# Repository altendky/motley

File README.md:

# Motley

Motley is a modular embedded-control project for building connected devices
without rebuilding the hardware integration and firmware infrastructure for
every application. The starting platform is ESP32-C6, C++, and Matter over
Thread, with Home Assistant as the initial integration target.

The first application is temperature control and humidity monitoring for an
animal enclosure. The broader goal is a reusable foundation for DIY sensing
and control: combine the boards you need, write application-specific behavior,
and reuse the sensor, output, storage and network integration.

**Early development:** the repository contains a buildable Matter identity
foundation and exploratory KiCad schematics and routed boards. Sensor drivers,
regulation algorithms, output-module firmware and the Matter application
interface are still to be implemented. The boards are designs to develop and
review, not tested products or a manufacturing release.

## Writing applications

The intended programming model keeps application decisions in a portable C++
core. It receives measurements, time and operation results, updates its state,
and describes the work it wants performed. Adapters handle sensors, outputs,
persistent storage and Matter; the same application logic can run in host tests
with controlled inputs.

For the enclosure application, that means concentrating on which sensor controls
which heater, setpoints, control modes, limits and fault responses. New
applications should be able to reuse the surrounding infrastructure rather
than couple their decisions directly to ESP-IDF or Matter APIs. This separation
is the [planned architecture](.rqml/adr/0001-portable-core-and-adapters.md);
an application framework and example application are still future work.

Extensibility includes separate sensor and output boards, addressed expansion,
and Qwiic access to both controller I2C buses. Additional interfaces, displays
and local controls are being considered. The hardware and software are intended
to grow through useful applications rather than require a fixed enclosure or
sensor/output count.

## First application: enclosure thermal control

The initial arrangement puts the controller outside a humid enclosure, with
remote temperature/humidity probes inside. Two independently controlled AC
heater or lamp outputs are planned, with a starting design target of **300 W
of resistive load per output at nominal 120 VAC**.

Planned output modes include slow, zero-cross-aligned whole-cycle switching for
heaters and phase-angle control for lamps. Each output module has its own MCU
for line-synchronous operation, current and voltage observations, and a series
cutoff relay. Temperature regulation will run locally in the device so it can
continue without Home Assistant or network access.

Exact regulation algorithms, sensor assignments, communication-loss policies
and the Matter control/reporting model are being defined. Higher output ratings,
international mains support and inductive loads are separate investigations;
the component ratings do not establish a finished system rating.

## Board designs

There are three KiCad designs. The initial two-output device uses one controller,
two copies of the output board and one sensor board. All currently use four
copper layers with ground/power planes and components on the front side.

| Board | High-level capabilities | Current outline |
| --- | --- | --- |
| [Controller and AC input](hardware/controller/motley-carrier.kicad_pro) | ESP32-C6 with 8 MB flash; Matter/Thread platform; isolated 5 V mains supply; automatic mains/USB logic-power selection; separately switched sensor supply; both I2C buses exposed through Qwiic; output connections and shared line timing | 95 × 80 mm |
| [Single AC output](hardware/controller/motley-ac-output.kicad_pro) | Local STM32 MCU; triac with random-phase isolated drive; series cutoff relay; isolated current/voltage feedback; branch fuse and configurable snubber; programming/recovery access | 90 × 87 mm |
| [Sensor multiplexer](hardware/controller/motley-sensors.kicad_pro) | Eight independently selected I2C branches with JST-SH/Qwiic-compatible connectors; selectable mux address; deployment and Qwiic upstream connections; cut-down layout for fewer ports | L-shaped, 80 × 40 mm overall |

The preferred expansion target is at least sixteen output boards, subject to
bus and power-budget work. Eight mux addresses provide sensor expansion, also
subject to electrical limits. These are design directions, not demonstrated
maximum configurations. Qwiic is a 3.3 V interface here; it is not the mains or
output-actuator power connection.

See the [board images](hardware/controller/generated/board-images/README.md)
for each copper layer, and the [hardware guide](hardware/controller/README.md)
for interfaces, preliminary parts and remaining engineering work.

## First development-build budget

These are **estimated costs in USD using the upper completion allowance, with
batch totals rounded to the nearest $25**, updated 2026-11-15 for the four-layer,
intelligent-output design. They combine actual
JLCPCB Economic fabrication/assembly quotes from that date's Gerbers and BOM/CPL
with estimated remaining hand-fitted parts and enclosure wiring. JLC's quotes
cover the selected available parts; they do not cover a complete device.
The subsequent exact-part revision has a
[new JLC quotation](docs/jlcpcb-quote-2026-11-16-exact-parts.md): $285.26 /
$312.08 / $419.13 for fabrication and partial assembly in the three scenarios.
The complete-controller budget below still uses the November 15 completion
allowances and needs reconciliation against those newer factory selections.

One complete controller means one controller board, one eight-port sensor board
and two output boards. Small-order minimums mean paying for spare boards even
when finishing only one device.

| Completed controllers | Boards assembled: controller / sensor / output | Estimated total batch cost | Per two-output controller |
| --- | --- | ---: | ---: |
| 1, minimum Economic assembly case | 2 / 2 / 2 | $350 | $350 |
| 2 | 2 / 2 / 5 | $450 | $225 |
| 5 | 5 / 5 / 10 | $800 | $160 |

Per-controller figures divide the rounded batch budget by the number finished,
including the cost of paid-for spares.

The allowance includes PCB fabrication and partial factory assembly, parts to
finish the required boards, heatsinks, mains cord/entry, outlets, panel USB and
internal wiring. Remaining parts require hand assembly. It excludes probes and
extensions, enclosure/mounting hardware, tools, shipping, tax and tariffs.
The selected [7Semi SHT45 probes](https://7semi.com/7semi-sht45-digital-humidity-and-temperature-sensor-probe/)
are about $13 each; probe count is independent of the eight available ports.

See the [budget basis](docs/development-build-costs.md) for quantity assumptions,
quoted charges, remaining-parts allowances and uncertainty. Part sourcing and
assembly eligibility can materially change these figures.

## Explore or contribute

- [Open work](https://github.com/altendky/motley/issues): current hardware,
  application and integration decisions.
- [Hardware candidates](docs/hardware-candidates.md) and
  [output-module design](docs/ac-output-module.md): component research and
  architectural context.
- [Development tools](docs/tooling.md), [firmware build](docs/firmware-build.md)
  and [Matter development](docs/matter-development.md): working with the code.
- [Requirements](requirements.rqml) and [architecture decisions](.rqml/adr/):
  agreed obligations, draft proposals and their rationale.

The first useful contributions are likely to be application design, firmware,
hardware review and practical packaging. Requirements distinguish planned
behavior from implementation and verification; build and CAD checks alone do
not establish that the assembled device works.

## Licensing

Original software and general text are licensed under **MIT OR Apache-2.0**.
Original hardware designs, including independently created symbols and
footprints, are licensed under **CERN-OHL-P-2.0**. Upstream-derived reusable
library parts retain their identified licenses and exceptions.

See the [license scope](LICENSE.md), [complete license texts](LICENSES/) and
[third-party notices](THIRD_PARTY_NOTICES.md).

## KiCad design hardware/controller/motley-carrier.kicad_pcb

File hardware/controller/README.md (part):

# Exploratory modular controller

Status: exploratory design, revised 2026-11-16; not a fabrication release.
All three PCB designs now use **four copper layers**, with low-voltage inner
ground and power planes and front-only assembly. Packed outlines are
**95 x 80 mm** for the carrier, **90 x 87 mm** for each output and an
**80 x 40 mm L** for the sensor board. The current
[four-layer review](four-layer-review.md) records the stackup, connected plane
regions, checks and remaining limits. Earlier
[output](output-routing-review.md) and
[carrier/sensor](carrier-sensor-routing-review.md) routing studies retain the
preceding two-layer evidence.
The [AC passive review](ac-passive-review.md) records the subsequent pulse-rated
component selection and LOW/HIGH assembly variants. The
[current JLC quote](../../docs/jlcpcb-quote-2026-11-16-exact-parts.md) includes the new LOW
passives in Economic assembly; physical electrical qualification remains pending.
The [exact purchasing selections](../../docs/hardware-exact-selections.md)
resolve the remaining connector/holder choices and record their mechanical
integration, including a LOW-only limit on the covered snubber caps. GOOSVN
mains terminals and JST PH output-bus headers pass actual Economic factory
assembly matching. Retail OGN holders, Samtec configuration headers and the
retained Omron relay remain hand-fitted in the current stock situation.
The later DNP USB-header/CC extension adds no default purchased components;
the quote retains its earlier input hashes and is not a new copper-revision quote.

The [intelligent-output review](intelligent-output-review.md) records the current
pin, default-state, power and ESD assessments, including the complete fresh
component/pin inventory. It supersedes the earlier direct-GPIO output portions
of the [pin-bias review](pin-bias-review.md). Output boards now have local MCUs,
isolated current/voltage observations and a shared buffered line reference.
Sensor-enable remains GPIO11 with a local 10k pull-down; sensor-bus reset pulls
still need off-domain review. Loaded drive, temperature/leakage, power budgets,
timing and contact-loss transients remain unqualified. Structural checks do not
close draft `MOT-HW-001/002` or qualify hardware defaults.

Native files now have hidden `Requirements` fields and explicit RQML links.
`uv run scripts/hardware_trace.py` checks 20 native source files and all 269
design footprints by hierarchical UUID identity. The fields record electrical
design applicability; MOT-HW-003 file links cover annotation integrity and
whole-file drift, not completion of the draft electrical requirements.
The fresh schematic inventory is 259 components / 737 symbol-pin identities
across the three designs; two output copies give 338 components / 942 pins per
complete unit. The 269 PCB footprints include ten board-only mechanical items.

The [ESD and access review](esd-access-review.md) records the added connector
clamps, per-port 100 ohm series resistors, marked local-GND touch copper and
optional wire-loop/post probe points. Its previous $3.31 protection estimate is
historical; the additional output bus/SYNC/power protection has not been requoted.
Bare access features require no purchased contacts. All fitted sensor components,
including
upstream clamps D60/D61 and the bare touch pad, are on the front. All boards
have top-side touch access, and assembly remains single-sided. System ESD,
clamp coordination, panel CC/shield and touch/clip qualification remain open.

## Scope and requirements boundary

This KiCad study makes the discussed controller, mux, probe and heater choices
concrete for review. The developer selected **three designs and four physical
boards per unit**: one integrated ESP32-C6 controller with AC input and isolated supply, two identical
single-output AC modules, and one mux with sensor connectors.
[ADR-0011](../../.rqml/adr/0011-single-output-modules-and-sensor-core.md)
records the board partition; [ADR-0014](../../.rqml/adr/0014-integrated-controller-and-switched-sensor-supply.md)
records the integrated controller and sensor supply. [Hardware candidates](../../docs/hardware-candidates.md)
records preliminary parts and unresolved engineering questions.

Under `MOT-PROC-001`, this remains a scoped exploratory exception for reviewing
schematics, interfaces, placement and trimming geometry before agreeing maintained
hardware requirements. It does not approve a mains design, implement firmware,
or qualify a PCB. `GOAL-MOT-SENSING` and `MOT-SENS-005` remain draft. Native
traceability tooling implements approved MOT-HW-003, while the electrical
study uses design-input relationships without claiming hardware verification.

The board experiments use four-layer routing and low-voltage ground/power
planes while retaining front-only assembly. The AC passive revision updates the
gate, snubber and voltage/timing detector networks on those routed studies.
Footprint/current/insulation qualification, enclosure
design, manufacturing release, purchasing and energization remain outside this
experiment. Passing structural checks does not establish mains safety or
functioning trimmed sensor boards.

## Open and review

Open any of these KiCad 10 projects in this directory using the
[pinned mise installation](../../docs/tooling.md#kicad); each has its own matching
root schematic, netlist and PCB:

| Project | Quantity per unit | Physical contents | Trial outline |
| --- | ---: | --- | --- |
| [motley-carrier.kicad_pro](motley-carrier.kicad_pro) | 1 | WROOM-N8, panel USB harness interface, automatic power selector, separate controller/sensor regulators, AC input, main fuse, MEAN WELL IRM-05-5, shared isolated line reference and inter-board connections | 95 x 80 mm |
| [motley-ac-output.kicad_pro](motley-ac-output.kicad_pro) | 2 identical copies | One output: STM32C011 and local logic supply/recovery, random-phase optotriac/triac, cutoff relay, isolated voltage/current feedback, branch fuse, configurable snubber, outlet and heatsink reservation; packed routing study | 90 x 87 mm |
| [motley-sensors.kicad_pro](motley-sensors.kicad_pro) | 1 | TCA9548A and support parts, upstream interface, eight QT sensor ports with pull-ups | L-shaped, 80 x 40 mm overall |

The former `motley-controller` monolithic root/project/PCB is replaced by these
three projects. Shared libraries remain in this directory. No board is panelized
with another, and no mechanical mating height or installed orientation is fixed.
The shapes are movable starting geometry, not minimum-size or enclosure claims.

**Stackup:** F.Cu signals/components, In1.Cu low-voltage GND, In2.Cu separate
low-voltage supply regions, B.Cu signals. The carrier additionally has an In2
GND corridor directly beneath its back-side USB pair. Raw actuator 5 V,
selected logic 5 V, controller 3.3 V and switched sensor 3.3 V remain distinct;
planes do not bypass source selection, switches or Qwiic power links. Mains and
PE retain their external-layer conductors, with no mains/PE planes. Antenna
and sensor-cut exclusions cover all four layers. [ADR-0021](../../.rqml/adr/0021-four-layer-ground-and-power-planes.md)
records the nominal 1.6 mm JLC04161H-7628 study construction and its limits.

**Board-size target:** keep each individual board's overall outline width and
height at or below **100 mm**, including the full untrimmed sensor board.
Exactly 100 mm meets the target. If design work suggests either dimension may
need to exceed it, raise the proposed size, reasons and alternatives with the
developer before proceeding with that enlargement. Larger boards can be agreed;
this is a strong target and discussion trigger, not a hard dimensional limit.
The sensor common area's width/depth trade remains flexible within this target.
Draft `MOT-HW-007/008` record the target and review process respectively.

All functional groups are unlocked. Hover an item and press **M** to move its
native group; enter the group to move individual items. The sensor core and bank
are grouped separately; the output module has separate power/MCU, heater,
feedback and access groups. The carrier keeps separate controller, USB/selection,
regulator, input/supply, shared line-reference and interface groups. Mounting
locations and the WROOM antenna reserve are provisional. Isolation corridors are
drawings, not qualified clearance rules.
The routed boards additionally have provisional copper rules. Moving their groups
now requires reviewing/reworking the attached routing; group movement alone
does not carry every inter-group connection or preserve the filled ground zones.

## Inter-board connections

Functional ownership is recorded in hidden `FunctionalGroup` component fields.
Run `./scripts/hardware_groups.py` to check allocation; pre-commit and CI enforce
the same check. See [the allocation guide](functional-groups.md) and
[group catalog](functional-groups.toml) for ownership boundaries and maintenance.

The connector numbers below define signal correspondence. The six-wire output
bus uses a continuous ribbon with keyed/shrouded 2×3, 2.54 mm Kinghelm headers,
HARTING 09185065813 IDC sockets and 3M 3801/06 cable. Output J14 is fitted;
parallel J22 is DNP. Nominal tap spacing is 50 mm, with allowance for strain
relief and service bends. See the [harness specification and electrical screen](../../docs/output-ribbon.md).
Sample mating, termination and operating qualification remain open. Other
low-voltage headers retain their study assignments.
Mechanical-only plated support holes are isolated from circuit nets. Mains
uses its separate terminal connection and must never use the signal interface.

| Link | Mating references | Pin order |
| --- | --- | --- |
| Sensor low voltage | Carrier J13 to sensor J12 | 1 GND, 2 switched 3V3_SENS, 3 SDA, 4 SCL, 5 mux RESET_N (GPIO21) |
| Output low voltage | One carrier J15 or J18 to continuous ribbon taps at each output J14 | 1 selected logic 5 V, 2 LP_I2C_SDA, 3 GND, 4 LP_I2C_SCL, 5 raw +5V_SYS, 6 LINE_SYNC |
| Optional output chaining | Each output J22, DNP by default | Electrically parallel with J14, identical numbered mapping |
| Output 1 mains | Carrier J16 to first output module J17 | 1 AC_L_FUSED, 2 AC_N, 3 PE |
| Output 2 mains | Carrier J19 to second output module J17 | 1 AC_L_FUSED, 2 AC_N, 3 PE |

Carrier contact 1 is `+5V_SELECTED`; the corresponding output net is `+5V_LOGIC`.
It feeds the output's local `+3V3_OUT` regulator, permitting USB-powered logic
commissioning without powering the raw 5 V relay/opto actuators. These two rails
are not tied together on the output. All boards share low-voltage GND.
Each module's MCU drives its own local `HEAT_EN`/`CUT_EN`; identity and a configured
I2C address determine the logical output, rather than the chosen carrier socket.
Each module's J10 is its own outlet; physical copies are not separate schematic
instances. Shared LINE_SYNC requires the same AC source/phase at every output.
Full and partial unplugging, missing GND and separately powered bus endpoints
remain unqualified.

Connect a continuous harness to only one carrier source. Its downstream
conductors remain intact when a tapped board is unplugged. The revised pin
order is incompatible with the earlier PH6 wiring. R42/R43 are now 2k2, with
no output-board I2C pull-ups; C205 bypasses raw 5 V at each output tap. Two
outputs have useful calculated timing/current margin. Sixteen remains a soft
exploration target requiring a different load/protection/supply assessment.

The main fuse is on the carrier; each heater retains its branch fuse on the
output board. Neutral and PE continue to both outlets. PE is not low-voltage
GND. The isolated supply remains ahead of heater switching so the controller
stays powered. The signal names apply to the current experiment; connector
ratings, wire sizes, source isolation and protective-earth implementation remain
engineering work.

## Optional Qwiic bench interfaces

The five-pin J13/J12 deployment link above is retained, including mux reset.
Six additional four-pin JST-SH sockets use standard Qwiic order:
**1 GND, 2 3.3 V, 3 SDA, 4 SCL**.

| Socket | Bus | Power contact |
| --- | --- | --- |
| Carrier J23/J25, HP pair | GPIO19 SDA / GPIO18 SCL, also used by J13 | Switched sensor rail through individual removable R44/R46 = 0 ohm; power OUT |
| Carrier J24/J26, LP pair | GPIO6 SDA / GPIO7 SCL; independent low-power I2C controller and shared output bus | Main +3V3 through individual removable R45/R47 = 0 ohm; power OUT |
| Sensor J10/J11 | Parallel mux upstream SDA/SCL, also used by J12/J13 | Shared connector-side power enters through removable R50 = 0 ohm |

Carrier-local pull-ups are 10k on the HP sensor bus to switched `+3V3_SENS`
and 2k2 on the LP bus to main `+3V3`, one pair per bus rather than per socket.
The mux keeps its local 4k7 upstream pull-ups
through separately removable R55/R56 = 0 ohm and retains its reset pull-up,
so it can be used without the carrier. Carrier port TVSs protect each signal pair and power
contact; the mux inputs share existing upstream protection. The farther J10
entry is roughly 20-26 mm from those clamps, so final routing may require local
protection. Entry/clamp/return geometry remains unqualified. The
carrier bench leaf is [qwiic-bench.kicad_sch](qwiic-bench.kicad_sch).

For standalone mux bench operation, **disconnect deployment links to another
host or supply**. Mux-to-mux five-pin links may pass through the same bench bus.
Use one controlling host and one power source on a connected bus. Carrier
Qwiic ports supply peripheral power; do not feed them from an external host's
power output. Removing a 0-ohm power link permits a separate peripheral supply
only with compatible powered bus endpoints: it does not isolate SDA/SCL or
permit driving an unpowered controller. Sensor-rail EN low is not isolation;
the regulator has an output-discharge path. The existing off-domain concerns
remain open. Enable sensor power and wait for startup before transactions.

Keep one SHT45 heater pulse active at a time across the connected system,
tracking its completion even if the mux channel is deselected. Its strongest
heater can draw 100 mA maximum; roughly 110 mA including other sensors/pulls
is an illustrative load, not a qualified budget. SparkFun gives a conservative
226 mA cable guideline. Include both buses' peripherals, USB entitlement,
regulator heating and cable drop before adding higher loads. The regulator's
600 mA headline rating is not an allowance per socket.
[SHT4x electrical limits](https://sensirion.com/media/documents/33FD6951/6A7C10A0/HT_DS_Datasheet_SHT4x_V7.3.pdf),
[Qwiic guidance](https://www.sparkfun.com/qwiic),
[AP2112 output discharge](https://www.diodes.com/datasheet/download/AP2112.pdf).
ADR-0017 and draft MOT-HW-009/010 record the interface direction; no firmware,
hot-plug, cable-length, load or ESD qualification is claimed.

## Multiple mux boards and addressing

Sensor SW1 is a three-position CTS 219-3MSTR DIP switch (JLC C3012353).
Each switch connects an address input to local 3.3 V, with a separate 10k
pull-down. OFF = 0, ON = 1; positions 1/2/3 have weights 1/2/4 for A0/A1/A2.
Address = **0x70 + A0 + 2*A1 + 4*A2**. All OFF selects 0x70. The selected
suffix ships ON, so set the desired unique address with power off; factory
position is not the configured baseline. The generic CTS-family land pattern
is preliminary, including actuator/height and assembly checks.

Sensor J12/J13 pass through all five deployment signals, including shared reset;
asserting reset affects all muxes on that reset chain. J10/J11 are parallel
upstream Qwiic connectors. Daisy-chain through these upstream connectors,
not through the eight switched sensor branches. Four-wire chains omit reset;
use power-cycle or separate reset access if hardware recovery is needed.

Carrier duplicate sockets permit branching on either bus. Choose chains or
branches without loops, duplicate supplies or extra controlling hosts. Upstream
Qwiic power contacts share their connector-side node: removing sensor R50
does not isolate those two external power sources from one another.

R55/R56 independently disconnect mux R2/R3 pull-ups. Remove excess upstream
pull-ups for the actual shared-bus load; ensure some suitable pulls remain.
Separate links avoid coupling SDA and SCL through a floating common resistor
feed. Downstream per-port pulls and local reset bias remain unchanged.

There are eight selectable mux addresses per bus, not a qualified eight-board
current/cable limit. All connected power, capacitance and pull-ups accumulate.
Firmware must deselect the previous mux before selecting another; writing a
different mux address does not clear the first device's latched selection.
Keep only one downstream branch visible across a bus when using identical-
address sensors. Draft MOT-SENS-006 records that future scheduler obligation;
no firmware behavior is implemented here. See ADR-0018.

## Sensor trimming plan

The common mux/interface area has no fixed width in connector positions. It
can trade width along the connector row against depth behind it; the row sets
the full board length. [ADR-0016](../../.rqml/adr/0016-flexible-sensor-core-aspect-ratio.md)
records this clarification. The geometry below describes the current placement
snapshot. Wider common circuitry would change the minimum retained cut-down
width and require the cuts to be reassessed.

The sensor board's long arm is 18 mm deep. Its 49 mm wide fixed leg contains the
mux, reset pull-up, decoupling, fitted upstream pull-ups, protection and five-pin interface.
The eight horizontal JST-SH sockets face the same enclosure wall at 10 mm center
spacing. Connector envelopes and end margins determine the 80 mm board length;
the core is entirely behind the first five connector positions. Side-wall
rotation and protrusion remain enclosure questions.

The three marked cuts retain ports **0 through N-1**, for N = 5 through 7;
the complete board retains all eight. Each removed port takes its two pull-ups
with it. Relative to the outline's upper-left corner, connector centers are at
x = 5 + 10*i mm and cut centers are x = 50, 60 and 70 mm. The
fixed leg survives every cut. An unwanted socket can be omitted or removed;
that does not require cutting away the core behind it. The layout reserves a
nominal 1 mm kerf and
0.25 mm positioning allowance; the cutting process is not selected or qualified.

Routing must keep all required core and retained-port connections on the
retained board. Downstream conductors must cross earlier cut lines, so those
lanes cannot be completely copper-free. Use deliberate separated crossings,
exclude pours/pads/vias from the cutting corridor, and provide post-cut edge
clearance, deburring and short/continuity checks. The routing review records
the retained-copper connectivity checks; the cutting process and actual
electrical operation still need physical qualification.

## Shared circuits and repeated placement

- [heater-channel.kicad_sch](heater-channel.kicad_sch) is instantiated once in
  the AC-output design. Build two copies of that board for two outlets. Its
  local MCU supplies its `HEAT_EN`/`CUT_EN` controls; `TRIAC_A1` stays local.
- [sensor-port.kicad_sch](sensor-port.kicad_sch) is instantiated eight times by
  [sensor-ports.kicad_sch](sensor-ports.kicad_sch). Each port has its own SDA/SCL
  pair and two pull-ups; power and ground are intentionally shared.

Native KiCad **Repeat Layout** was exercised on the earlier combined study.
This revision retains one heater's geometry on the output module and places the
sensor instances at 10 mm pitch. These transforms were applied programmatically;
no new GUI repeat/autoplace operation is claimed. One heater and eight sensor
placement areas remain. Output reuse comes from building one board twice;
sensor ports still have repeated placement within one board.

To propagate a sensor template placement edit, enter its group, select
`SENSOR_PORT_0`, then use **Tools -> Multi-Channel -> Repeat Layout**. Enable
footprint placement only; disable routing, other-item copying, target grouping
and locked-item overrides. Review the result and DRC. Editing the shared
schematic changes its instances, but PCB placement only propagates when copied.

## Review exports and footprint limitations

The two combined review files retain their original paths:
`review/motley-controller.pdf` contains all three schematics (24 pages), and
`review/motley-controller-placement.pdf` contains the three front placements
(three pages). Both use carrier, AC output, then sensor board order, with a
bookmark for each board. These ignored PDFs are earlier review snapshots;
the 2026-11-16 passive revision updates native CAD and committed SVGs, and
the PDFs need regeneration before reviewing that revision.

`review/motley-ac-output-routing.pdf` adds four copper pages in stack order,
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
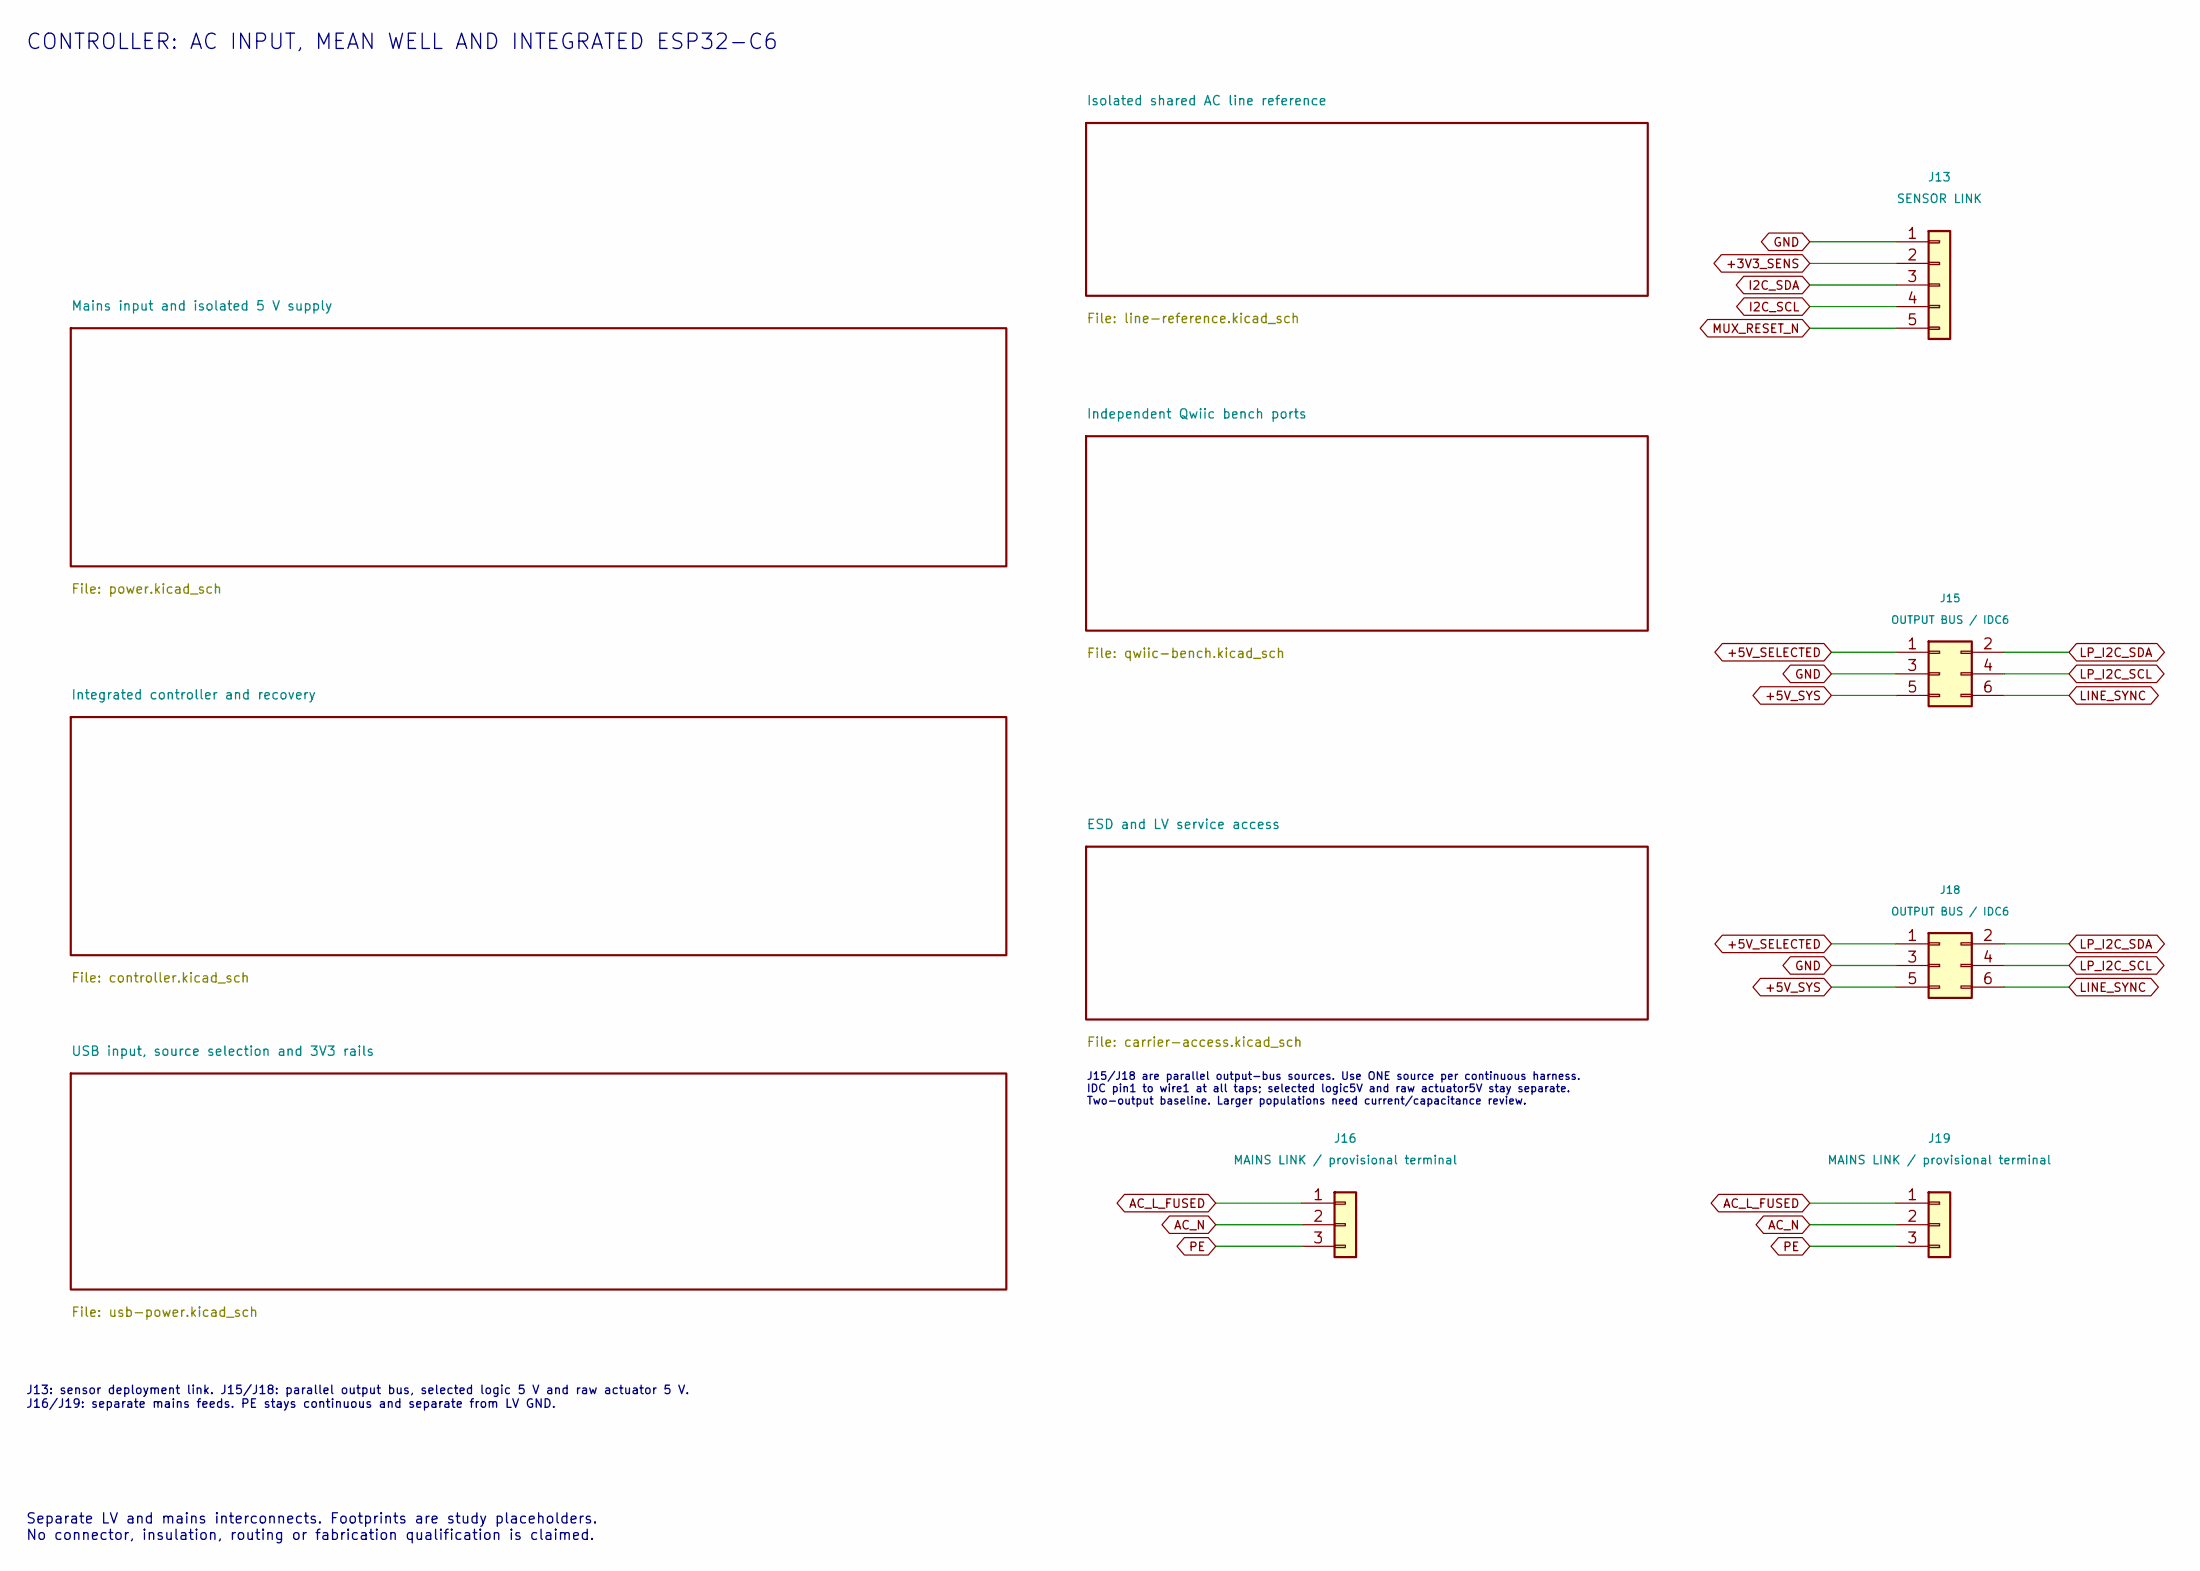
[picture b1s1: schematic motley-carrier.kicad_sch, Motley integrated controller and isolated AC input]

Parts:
J13: SENSOR LINK; PinHeader_1x05_P2.54mm_Vertical
J15, J18: OUTPUT BUS / IDC6; Kinghelm_KH-2.54PH180-2X3P-L8.9_Vertical; MPN KH-2.54PH180-2X3P-L8.9; LCSC C5157626
J16, J19: MAINS LINK / provisional terminal; TerminalBlock_GOOSVN_GS007S_P5.08mm_1x03_Horizontal; MPN GS007S-5.08-03P-11-00A(H); LCSC C5142603

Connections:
+3V3_SENS: J13.2; also elsewhere on the board
+5V_SELECTED: J15.1, J18.1; also elsewhere on the board
+5V_SYS: J15.5, J18.5; also elsewhere on the board
AC_L_FUSED: J16.1, J19.1; also elsewhere on the board
AC_N: J16.2, J19.2; also elsewhere on the board
GND: J13.1, J15.3, J18.3; also elsewhere on the board
I2C_SCL: J13.4; also elsewhere on the board
I2C_SDA: J13.3; also elsewhere on the board
LINE_SYNC: J15.6, J18.6; also elsewhere on the board
LP_I2C_SCL: J15.4, J18.4; also elsewhere on the board
LP_I2C_SDA: J15.2, J18.2; also elsewhere on the board
MUX_RESET_N: J13.5; also elsewhere on the board
PE: J16.3, J19.3; also elsewhere on the board

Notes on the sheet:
J13: sensor deployment link. J15/J18: parallel output bus, selected logic 5 V and raw actuator 5 V. J16/J19: separate mains feeds. PE stays continuous and separate from LV GND.
Separate LV and mains interconnects. Footprints are study placeholders. No connector, insulation, routing or fabrication qualification is claimed.
CONTROLLER: AC INPUT, MEAN WELL AND INTEGRATED ESP32-C6
J15/J18 are parallel output-bus sources. Use ONE source per continuous harness. IDC pin1 to wire1 at all taps; selected logic5V and raw actuator5V stay separate. Two-output baseline. Larger populations need current/capacitance review.

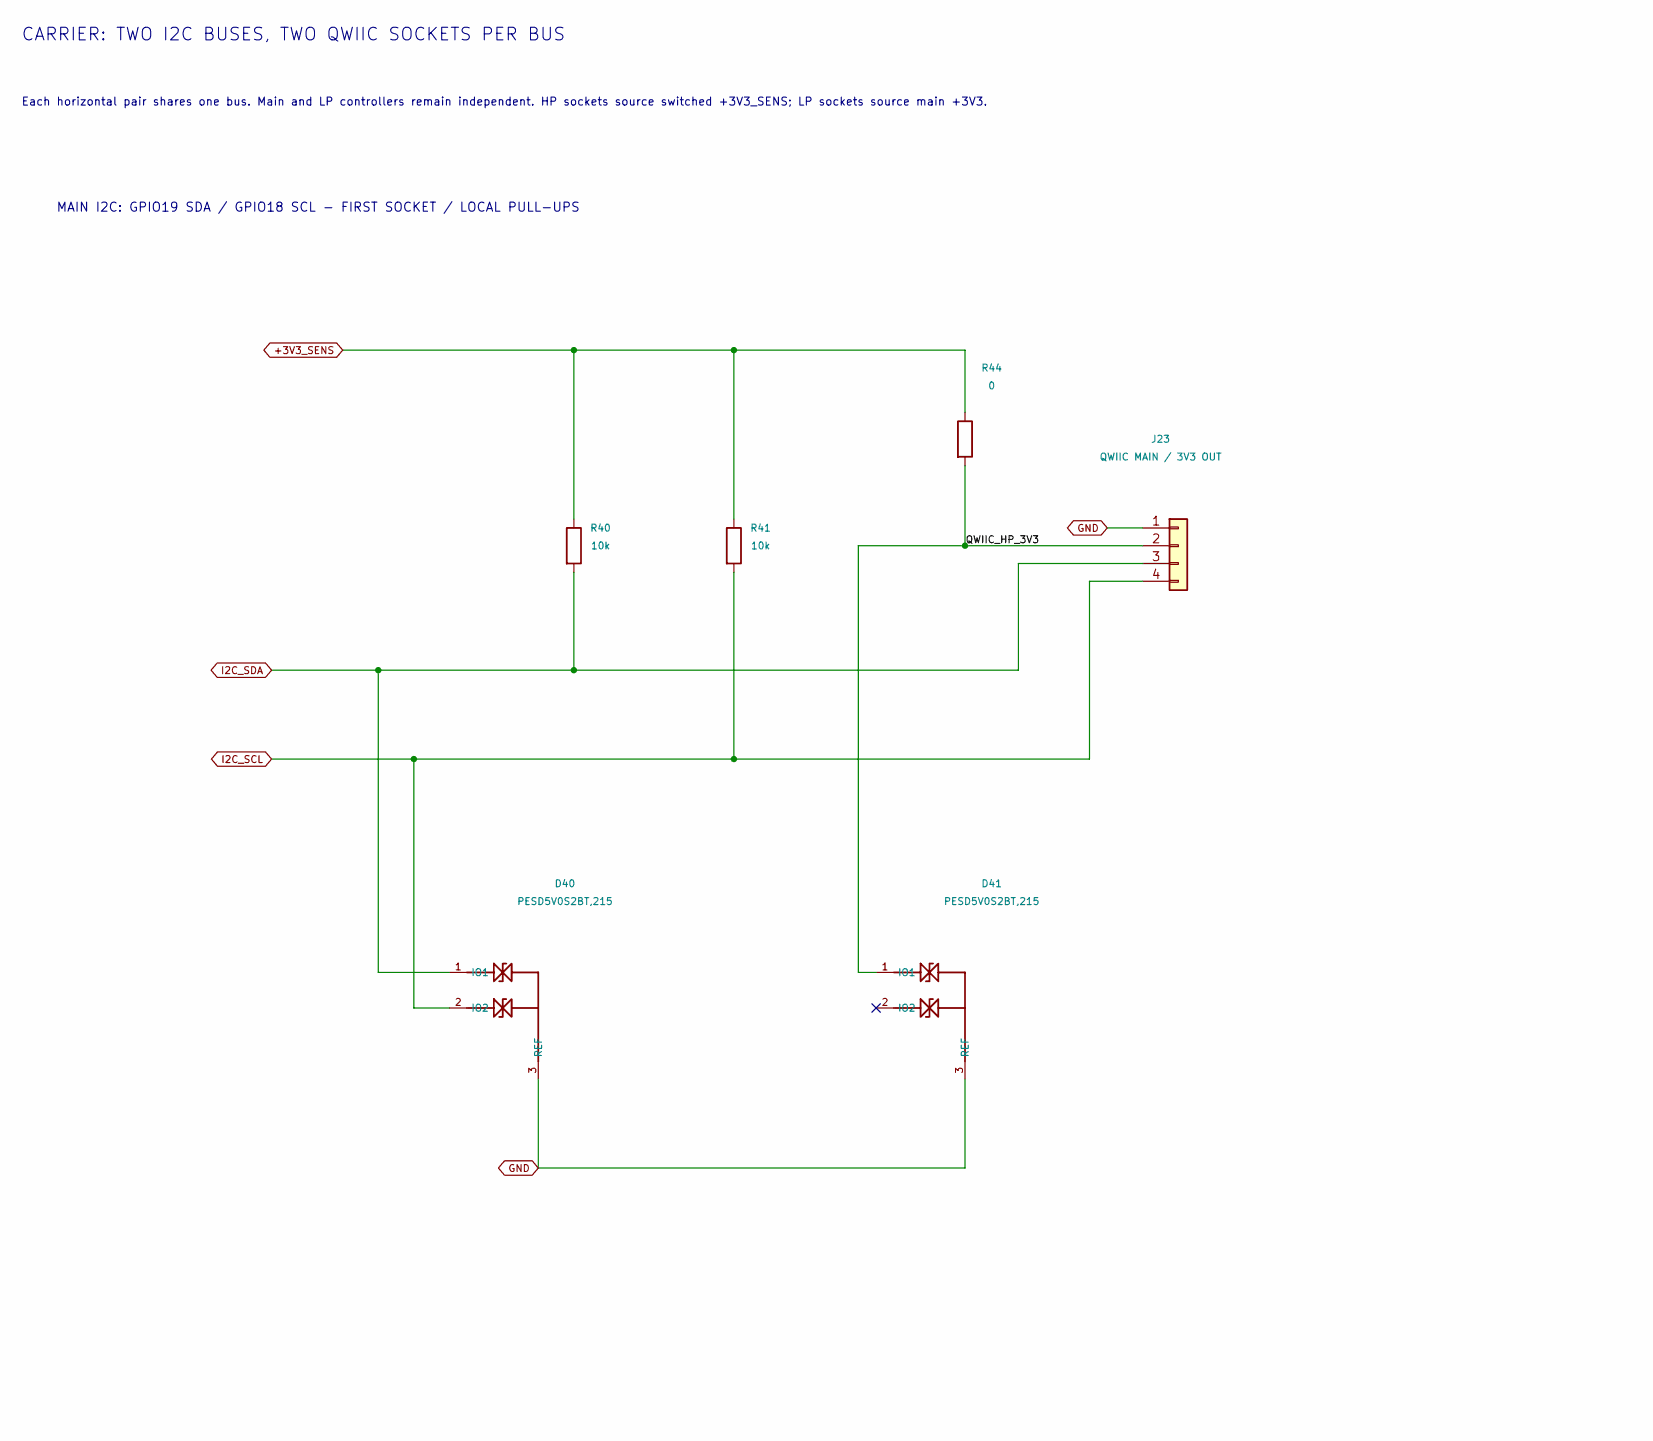
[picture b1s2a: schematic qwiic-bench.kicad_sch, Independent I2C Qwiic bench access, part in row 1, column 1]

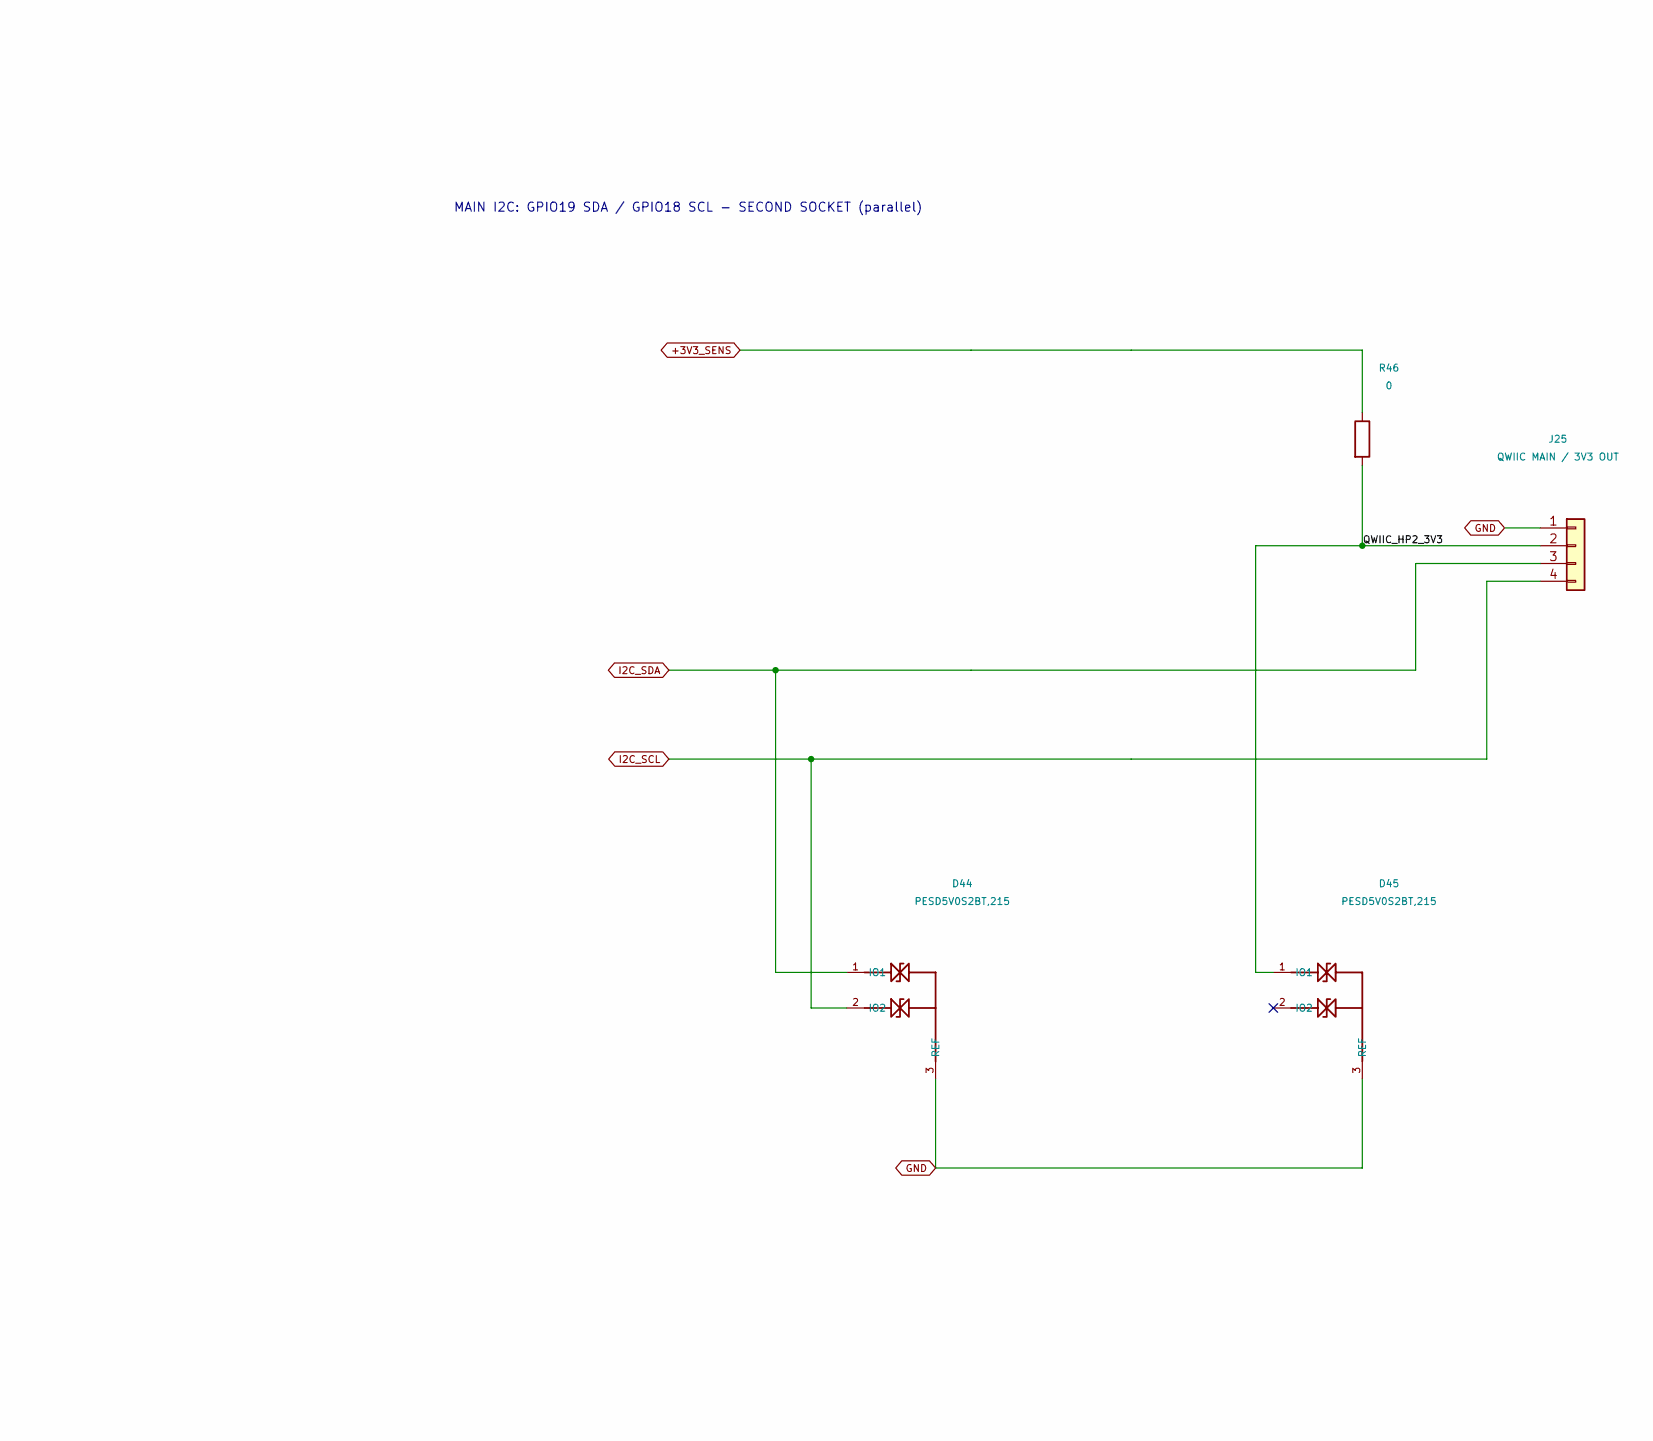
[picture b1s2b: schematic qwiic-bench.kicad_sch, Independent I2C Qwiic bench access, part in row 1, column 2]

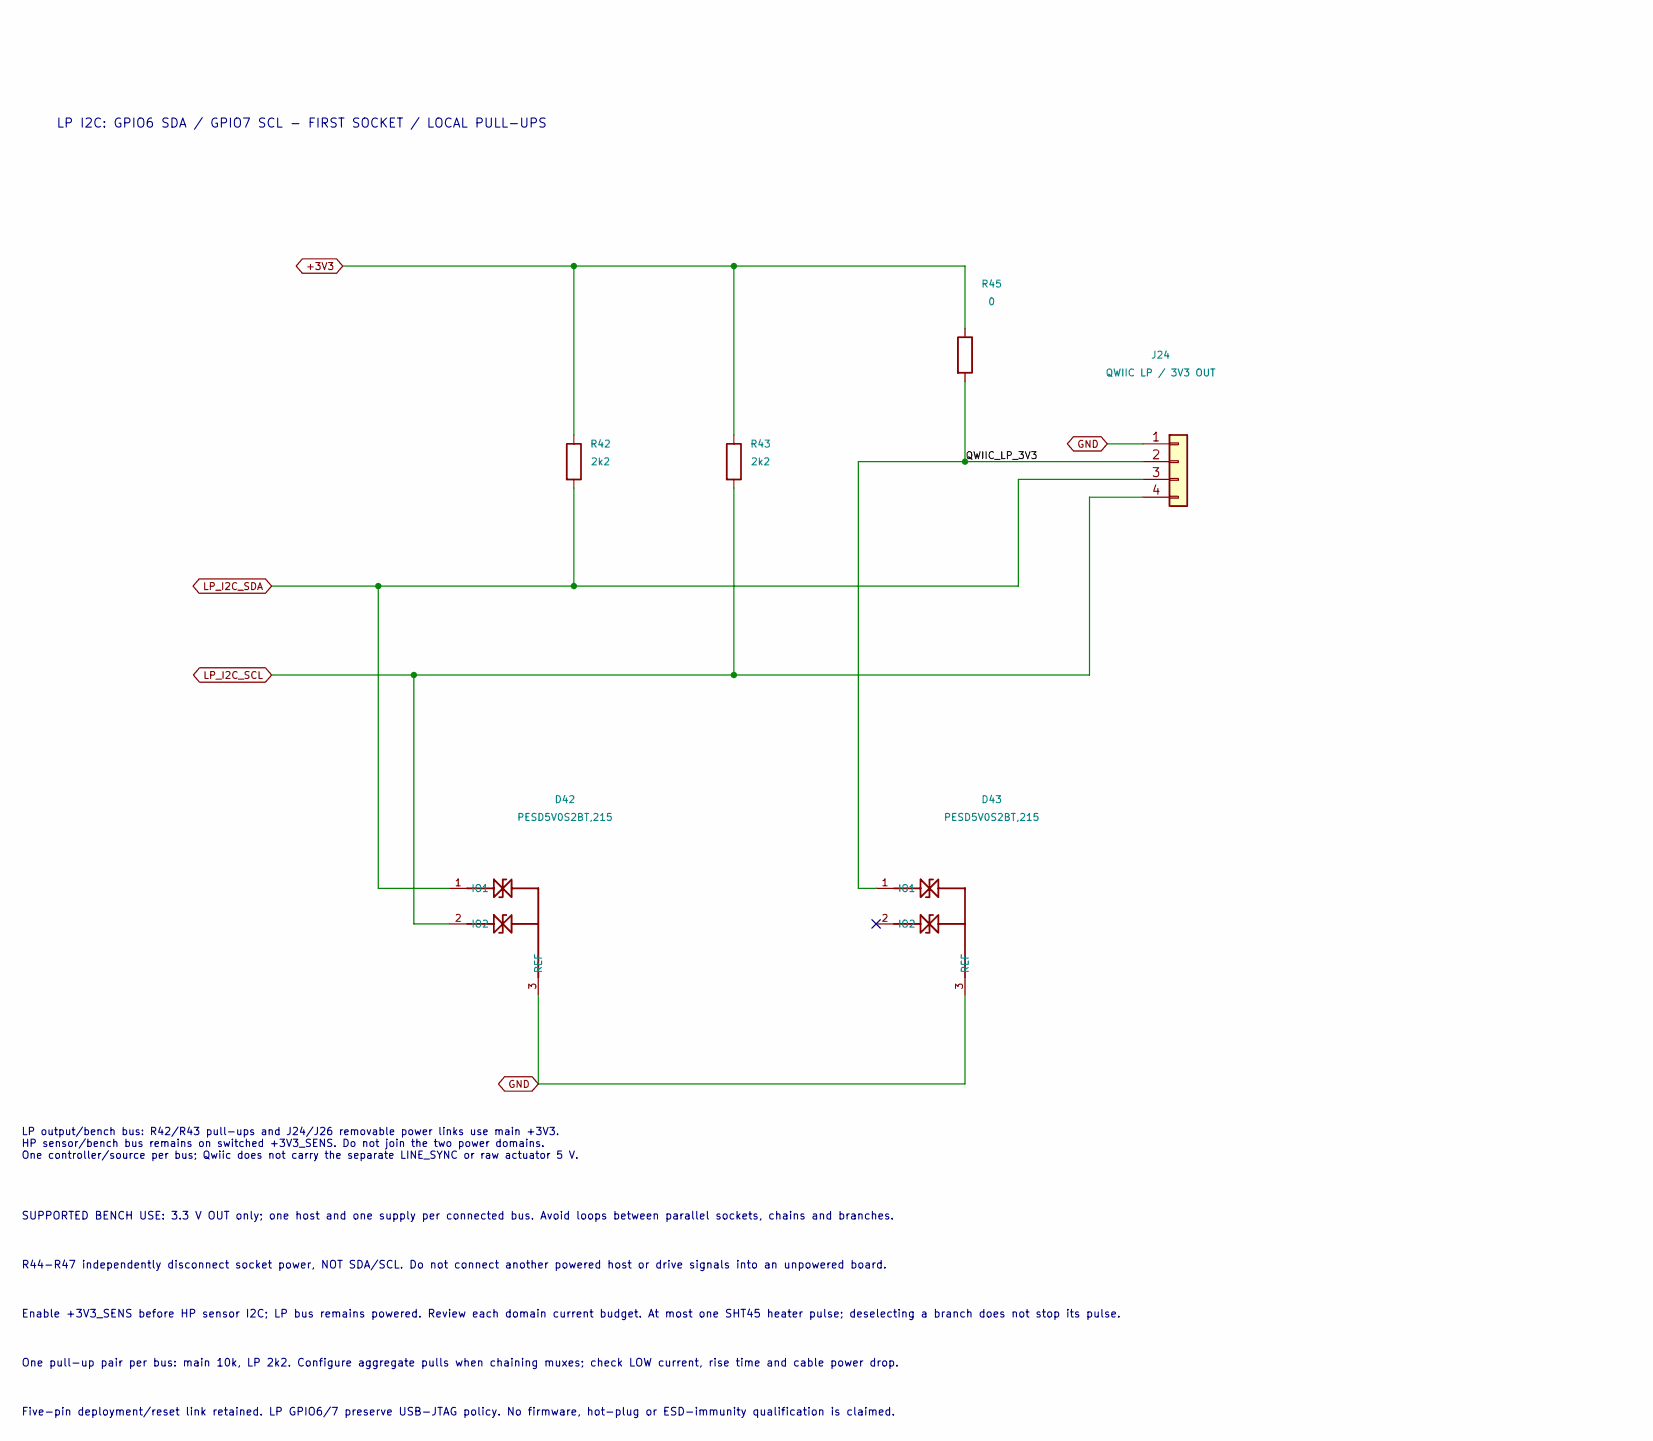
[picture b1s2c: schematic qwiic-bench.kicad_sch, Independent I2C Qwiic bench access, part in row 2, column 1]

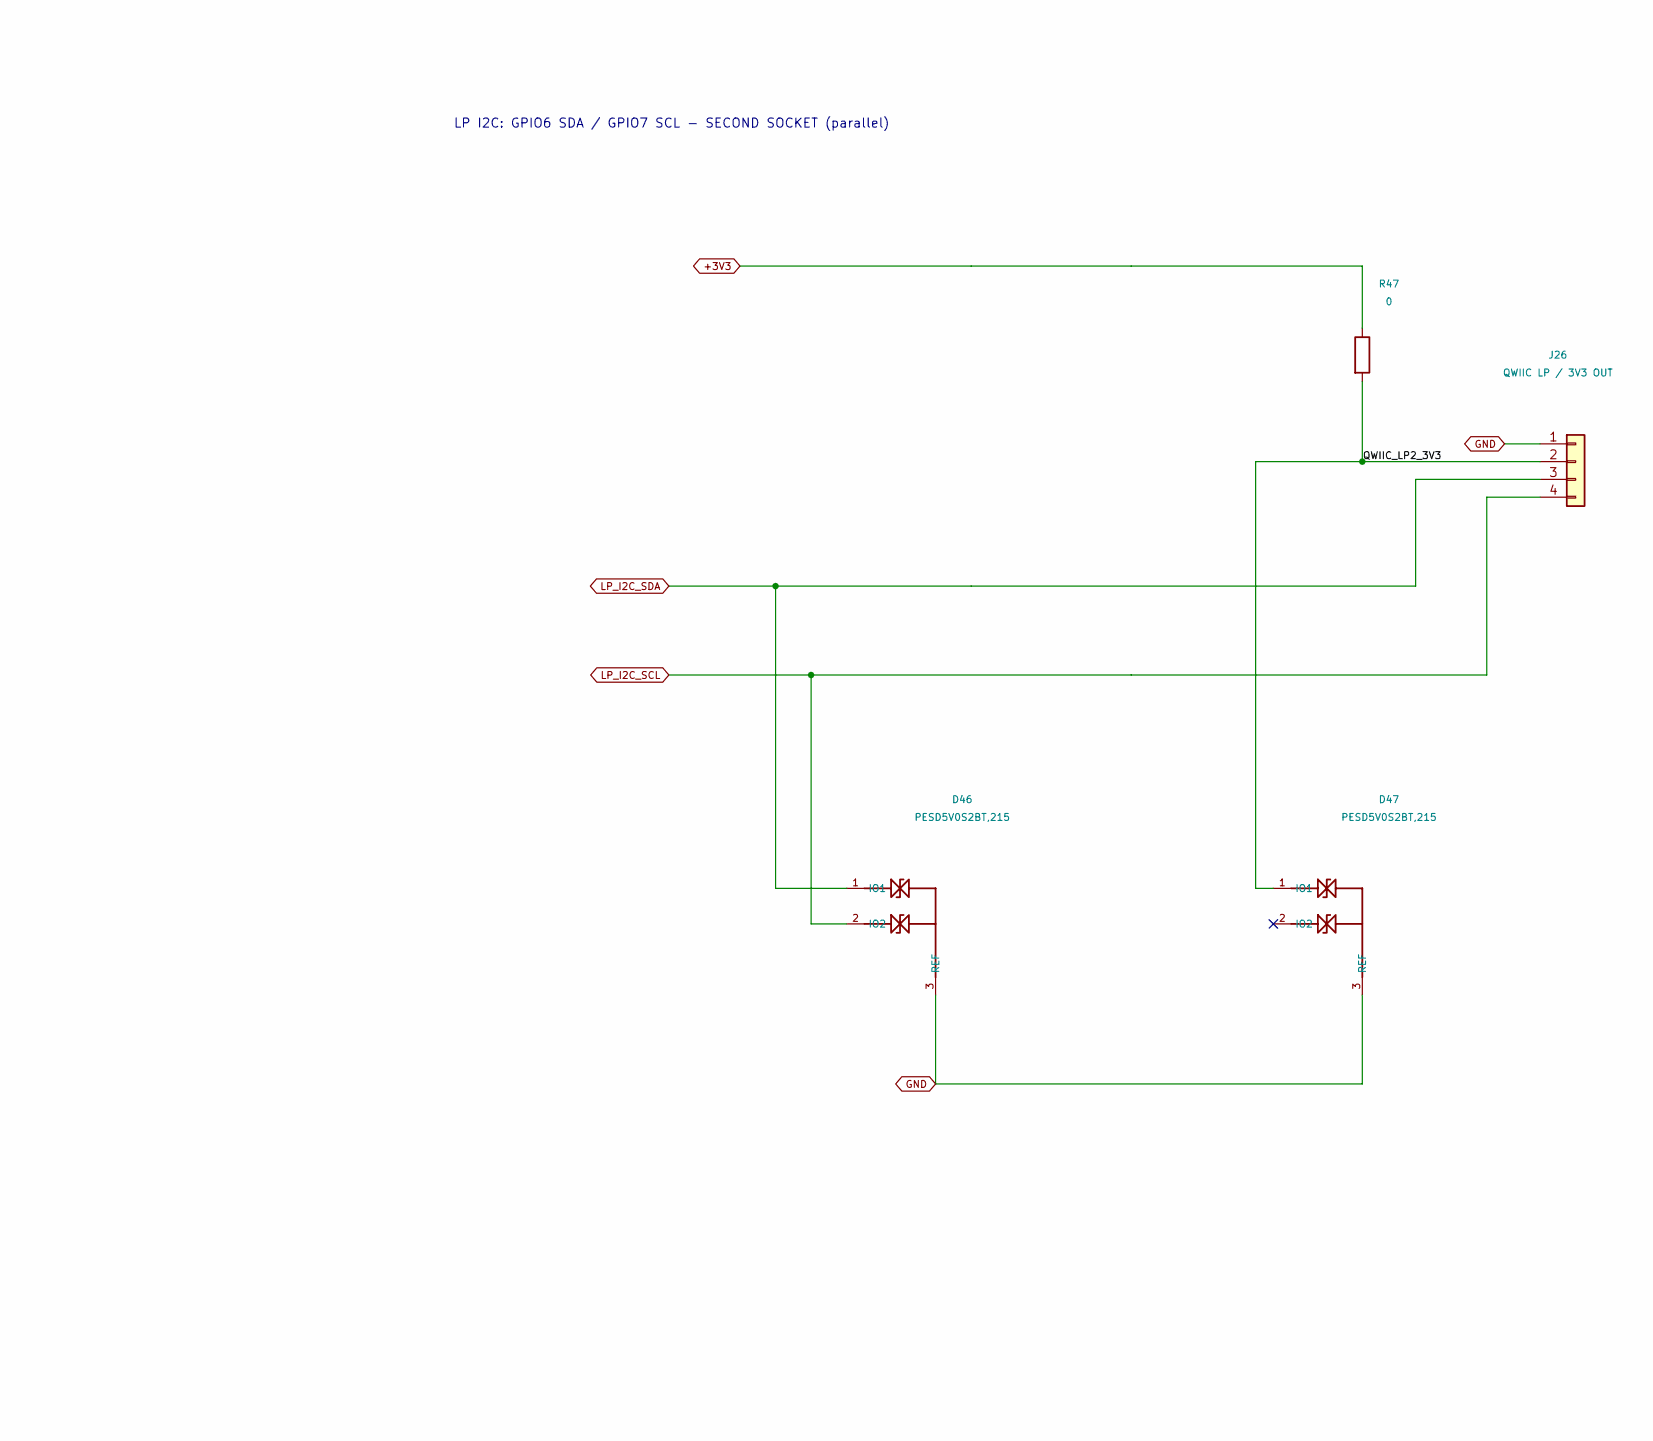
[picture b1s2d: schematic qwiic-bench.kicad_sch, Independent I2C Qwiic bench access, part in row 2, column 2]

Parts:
D40, D41, D42, D43, D44, D45, D46, D47: PESD5V0S2BT,215; SOT-23
J23, J25: QWIIC MAIN / 3V3 OUT; JST_SH_SM04B-SRSS-TB_1x04-1MP_P1.00mm_Horizontal
J24, J26: QWIIC LP / 3V3 OUT; JST_SH_SM04B-SRSS-TB_1x04-1MP_P1.00mm_Horizontal
R40, R41: 10k; R_0805_2012Metric
R42, R43: 2k2; R_0805_2012Metric; MPN 0805W8F2201T5E; LCSC C17520
R44, R45, R46, R47: 0; R_0805_2012Metric

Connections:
+3V3: R42.1, R43.1, R45.1, R47.1; also elsewhere on the board
+3V3_SENS: R40.1, R41.1, R44.1, R46.1; also elsewhere on the board
/Independent Qwiic bench ports/QWIIC_HP2_3V3: D45.1 (IO1), J25.2, R46.2
/Independent Qwiic bench ports/QWIIC_HP_3V3: D41.1 (IO1), J23.2, R44.2
/Independent Qwiic bench ports/QWIIC_LP2_3V3: D47.1 (IO1), J26.2, R47.2
/Independent Qwiic bench ports/QWIIC_LP_3V3: D43.1 (IO1), J24.2, R45.2
GND: D40.3 (REF), D41.3 (REF), D42.3 (REF), D43.3 (REF), D44.3 (REF), D45.3 (REF), D46.3 (REF), D47.3 (REF), J23.1, J24.1, J25.1, J26.1; also elsewhere on the board
I2C_SCL: D40.2 (IO2), D44.2 (IO2), J23.4, J25.4, R41.2; also elsewhere on the board
I2C_SDA: D40.1 (IO1), D44.1 (IO1), J23.3, J25.3, R40.2; also elsewhere on the board
LP_I2C_SCL: D42.2 (IO2), D46.2 (IO2), J24.4, J26.4, R43.2; also elsewhere on the board
LP_I2C_SDA: D42.1 (IO1), D46.1 (IO1), J24.3, J26.3, R42.2; also elsewhere on the board

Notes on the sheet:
LP I2C: GPIO6 SDA / GPIO7 SCL - SECOND SOCKET (parallel)
R44-R47 independently disconnect socket power, NOT SDA/SCL. Do not connect another powered host or drive signals into an unpowered board.
One pull-up pair per bus: main 10k, LP 2k2. Configure aggregate pulls when chaining muxes; check LOW current, rise time and cable power drop.
MAIN I2C: GPIO19 SDA / GPIO18 SCL - FIRST SOCKET / LOCAL PULL-UPS
LP output/bench bus: R42/R43 pull-ups and J24/J26 removable power links use main +3V3. HP sensor/bench bus remains on switched +3V3_SENS. Do not join the two power domains. One controller/source per bus; Qwiic does not carry the separate LINE_SYNC or raw actuator 5 V.
Each horizontal pair shares one bus. Main and LP controllers remain independent. HP sockets source switched +3V3_SENS; LP sockets source main +3V3.
CARRIER: TWO I2C BUSES, TWO QWIIC SOCKETS PER BUS
MAIN I2C: GPIO19 SDA / GPIO18 SCL - SECOND SOCKET (parallel)
Five-pin deployment/reset link retained. LP GPIO6/7 preserve USB-JTAG policy. No firmware, hot-plug or ESD-immunity qualification is claimed.
SUPPORTED BENCH USE: 3.3 V OUT only; one host and one supply per connected bus. Avoid loops between parallel sockets, chains and branches.
Enable +3V3_SENS before HP sensor I2C; LP bus remains powered. Review each domain current budget. At most one SHT45 heater pulse; deselecting a branch does not stop its pulse.
LP I2C: GPIO6 SDA / GPIO7 SCL - FIRST SOCKET / LOCAL PULL-UPS

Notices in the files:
hardware/controller/README.md:
Original hardware and independently created library parts use CERN-OHL-P-2.0;
